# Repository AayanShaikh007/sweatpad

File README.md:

# Sweatpad- the hackpad for sweats
**Scroll down to see the finished product!**

I always found most gaming keyboards to be difficult to use and somewhat non ergonomic. This prompted me to create the sweatpad, a shortened keyboard with only the keys that you may need to play most fps games. It also features RGB lighting, a OLED display to show data/modes.

## Complete Assembly (without keys):
Some images of what the finished product should approximately look like. 

## PCB and Schematic

## Case and Exploded View

## BOM 
- 1 SEEEDUINO XIAO RP2040
- 16x MX-Style switches (preferrably MX-Brown)
- 16x 1N4148 diodes
- 1x SSD1306 LED (I2C)
- 16 Blank DSA keycaps (White)
- 16x SK6812 MINI-E LEDs
- 4x M3x16mm screws, and corresponding nuts

## Notes
Although this project should have been really simple, i overcomplicated it by adding a bunch of switches because of my original idea for the project, but at least now it would be easier for me to design my full/60% keyboard. The PCB was larger than the 100x100 mm restriction, so i had to shorten it, leading to some unsightly changes in the case- but they shouldn't have any effect on the functionality. 

# Finished Product

# Youtube Demo Link

https://youtu.be/8_cZmQdGrSU

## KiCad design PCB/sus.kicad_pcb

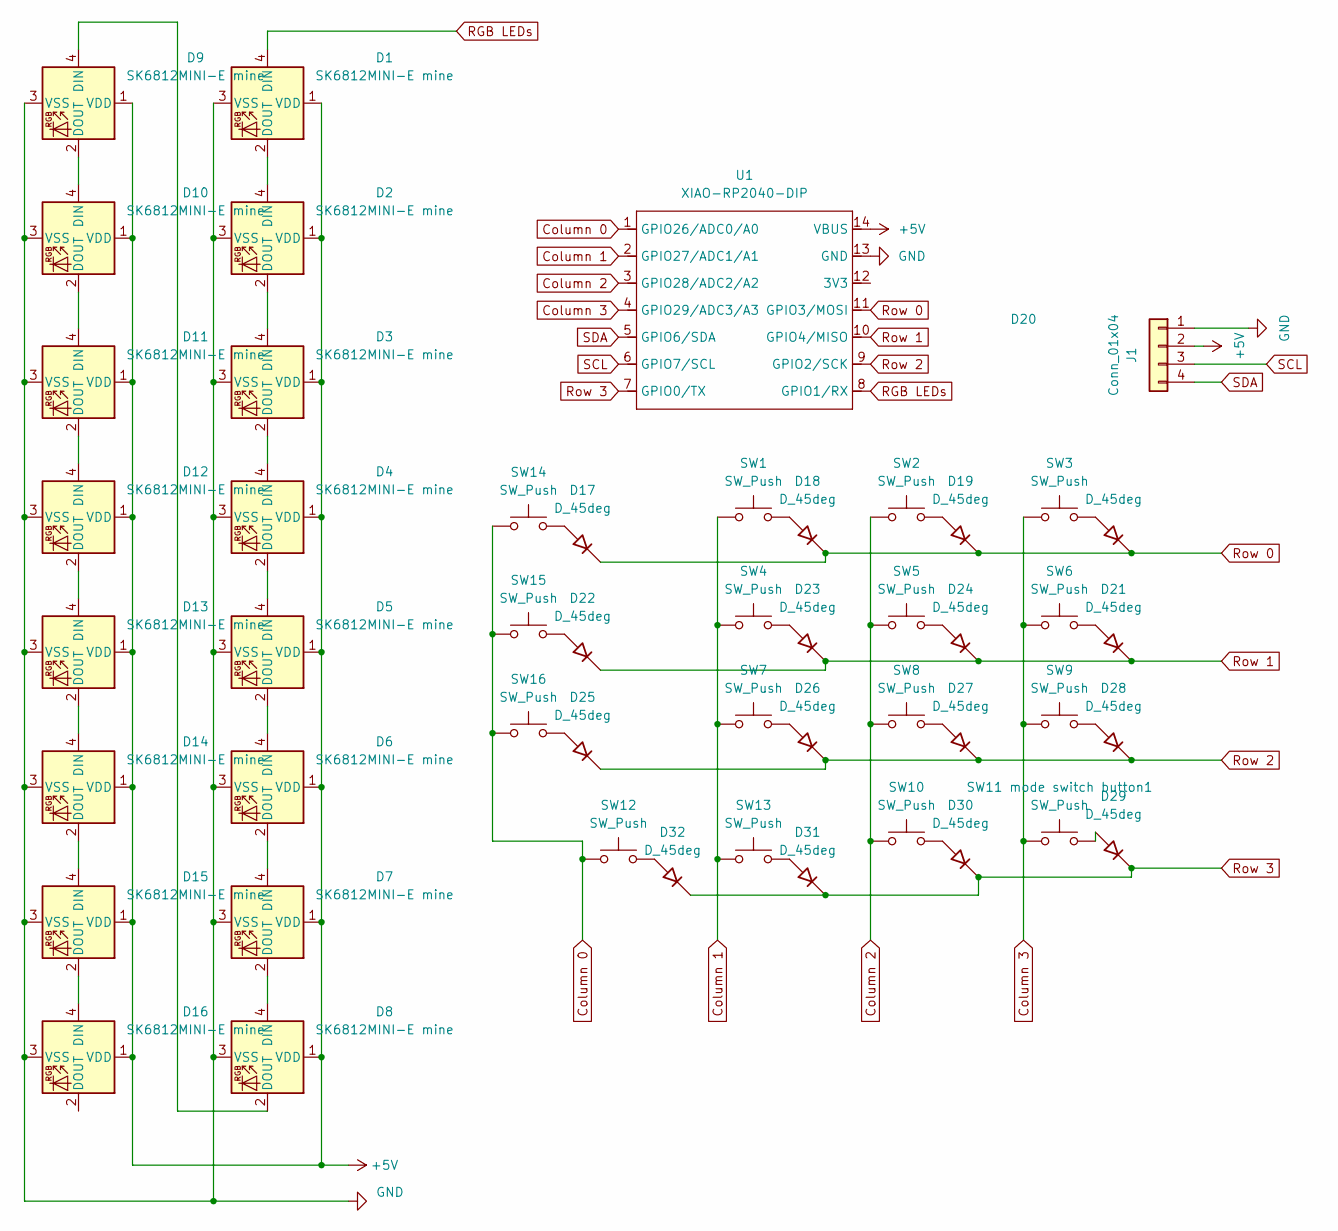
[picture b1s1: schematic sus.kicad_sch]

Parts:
D1, D2, D3, D4, D5, D6, D7, D8, D9, D10, D11, D12, D13, D14, D15, D16: SK6812MINI-E mine; BAcklight
D17, D18, D19, D20, D21, D22, D23, D24, D25, D26, D27, D28, D29, D30, D31, D32: D_45deg; DO35-7
J1: Conn_01x04; SSD1306-0.91-OLED-4pin-128x32
SW1, SW2: SW_Push; SW_Cherry_MX_2.25u_PCB
SW3: SW_Push; SW_Cherry_MX_1.75u_PCB
SW4: SW_Push; SW_Cherry_MX_1.50u_PCB
SW5, SW6, SW7, SW8, SW9, SW10, SW11 mode switch button1, SW12, SW13, SW14, SW15, SW16: SW_Push; SW_Cherry_MX_1.00u_PCB
U1: XIAO-RP2040-DIP

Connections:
+5V: D1.1 (VDD), D2.1 (VDD), D3.1 (VDD), D4.1 (VDD), D5.1 (VDD), D6.1 (VDD), D7.1 (VDD), D8.1 (VDD), D9.1 (VDD), D10.1 (VDD), D11.1 (VDD), D12.1 (VDD), D13.1 (VDD), D14.1 (VDD), D15.1 (VDD), D16.1 (VDD), J1.2, U1.14 (VBUS)
Column 0: SW12.1, SW14.1, SW15.1, SW16.1, U1.1 (GPIO26/ADC0/A0)
Column 1: SW1.1, SW4.1, SW7.1, SW13.1, U1.2 (GPIO27/ADC1/A1)
Column 2: SW2.1, SW5.1, SW8.1, SW10.1, U1.3 (GPIO28/ADC2/A2)
Column 3: SW3.1, SW6.1, SW9.1, SW11 mode switch button1.1, U1.4 (GPIO29/ADC3/A3)
GND: D1.3 (VSS), D2.3 (VSS), D3.3 (VSS), D4.3 (VSS), D5.3 (VSS), D6.3 (VSS), D7.3 (VSS), D8.3 (VSS), D9.3 (VSS), D10.3 (VSS), D11.3 (VSS), D12.3 (VSS), D13.3 (VSS), D14.3 (VSS), D15.3 (VSS), D16.3 (VSS), J1.1, U1.13 (GND)
unnamed: D1.2 (DOUT), D2.4 (DIN)
unnamed: D2.2 (DOUT), D3.4 (DIN)
unnamed: D3.2 (DOUT), D4.4 (DIN)
unnamed: D4.2 (DOUT), D5.4 (DIN)
unnamed: D5.2 (DOUT), D6.4 (DIN)
unnamed: D6.2 (DOUT), D7.4 (DIN)
unnamed: D7.2 (DOUT), D8.4 (DIN)
unnamed: D8.2 (DOUT), D9.4 (DIN)
unnamed: D9.2 (DOUT), D10.4 (DIN)
unnamed: D10.2 (DOUT), D11.4 (DIN)
unnamed: D11.2 (DOUT), D12.4 (DIN)
unnamed: D12.2 (DOUT), D13.4 (DIN)
unnamed: D13.2 (DOUT), D14.4 (DIN)
unnamed: D14.2 (DOUT), D15.4 (DIN)
unnamed: D15.2 (DOUT), D16.4 (DIN)
unnamed: D17.2 (A), SW14.2
unnamed: D18.2 (A), SW1.2
unnamed: D19.2 (A), SW2.2
unnamed: D20.2 (A), SW3.2
unnamed: D21.2 (A), SW6.2
unnamed: D22.2 (A), SW15.2
unnamed: D23.2 (A), SW4.2
unnamed: D24.2 (A), SW5.2
unnamed: D25.2 (A), SW16.2
unnamed: D26.2 (A), SW7.2
unnamed: D27.2 (A), SW8.2
unnamed: D28.2 (A), SW9.2
unnamed: D29.2 (A), SW11 mode switch button1.2
unnamed: D30.2 (A), SW10.2
unnamed: D31.2 (A), SW13.2
unnamed: D32.2 (A), SW12.2
RGB LEDs: D1.4 (DIN), U1.8 (GPIO1/RX)
Row 0: D17.1 (K), D18.1 (K), D19.1 (K), D20.1 (K), U1.11 (GPIO3/MOSI)
Row 1: D21.1 (K), D22.1 (K), D23.1 (K), D24.1 (K), U1.10 (GPIO4/MISO)
Row 2: D25.1 (K), D26.1 (K), D27.1 (K), D28.1 (K), U1.9 (GPIO2/SCK)
Row 3: D29.1 (K), D30.1 (K), D31.1 (K), D32.1 (K), U1.7 (GPIO0/TX)
SCL: J1.3, U1.6 (GPIO7/SCL)
SDA: J1.4, U1.5 (GPIO6/SDA)

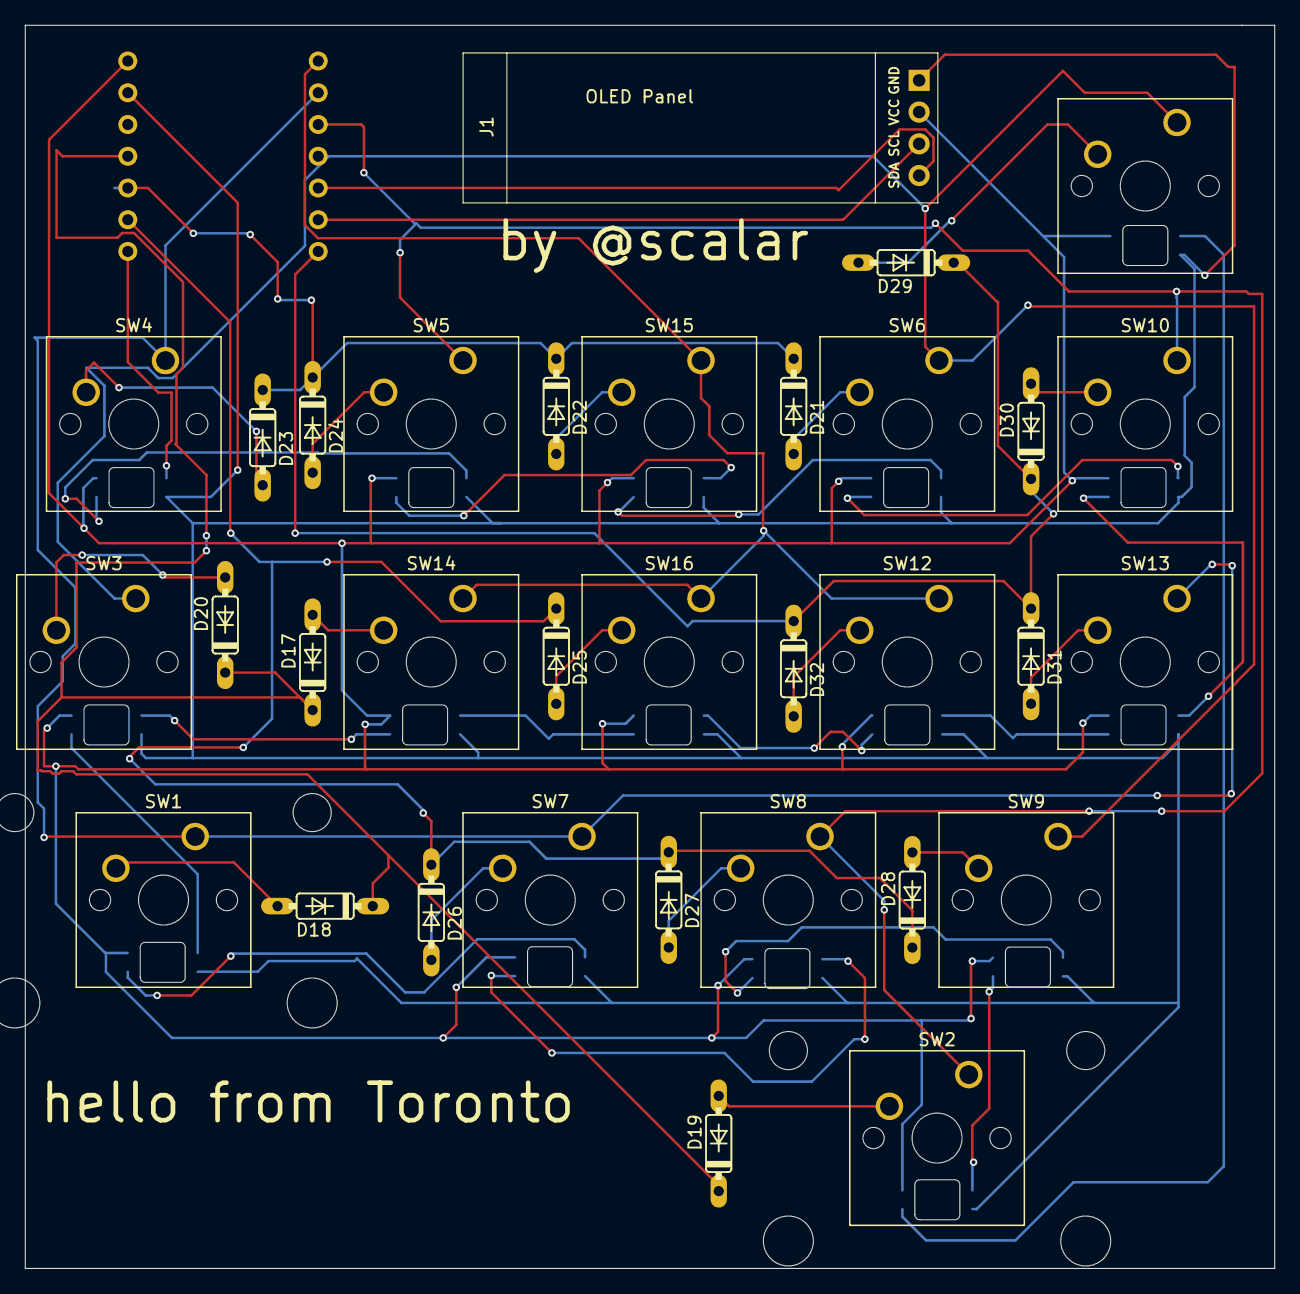
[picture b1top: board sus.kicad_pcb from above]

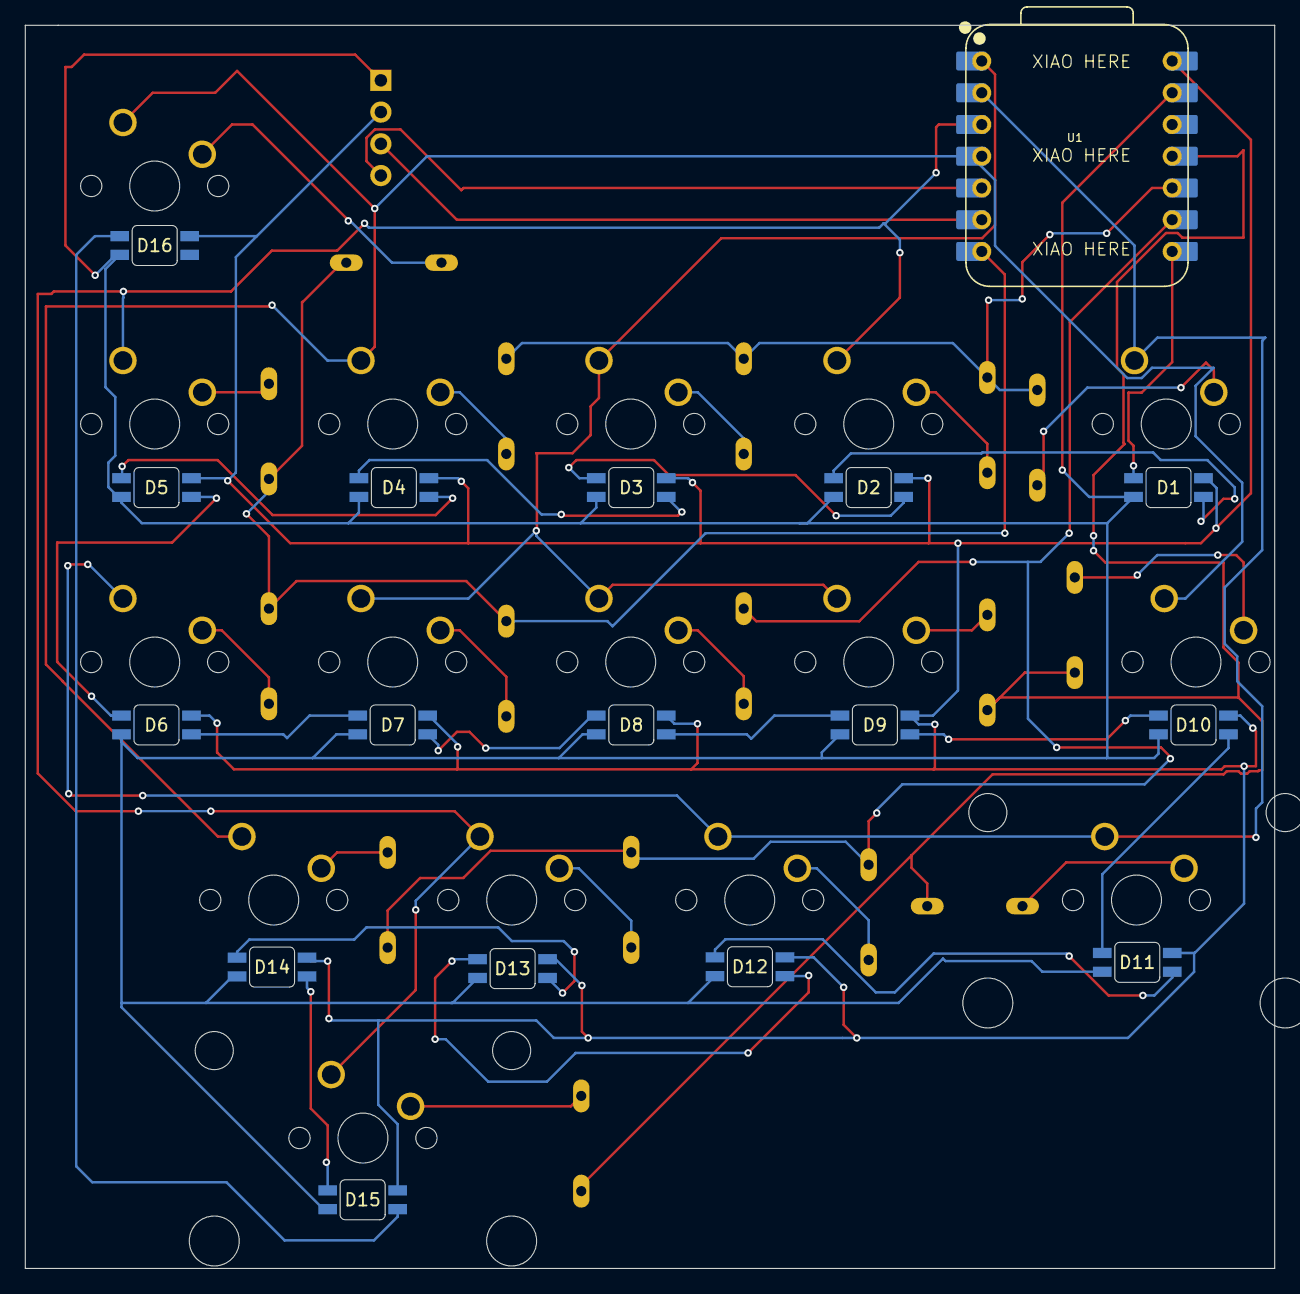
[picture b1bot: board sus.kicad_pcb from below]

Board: 2 copper layers, 100.0 x 99.5 mm, 50 parts (17 on the bottom side), 44 nets.

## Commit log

2025-06-13 Update journal.md formatting
2025-06-13 adding oled hole changes
2026-05-09 Refactor main.py by removing unused code and updating pins
    Removed unused imports and updated pin assignments for the keyboard.
